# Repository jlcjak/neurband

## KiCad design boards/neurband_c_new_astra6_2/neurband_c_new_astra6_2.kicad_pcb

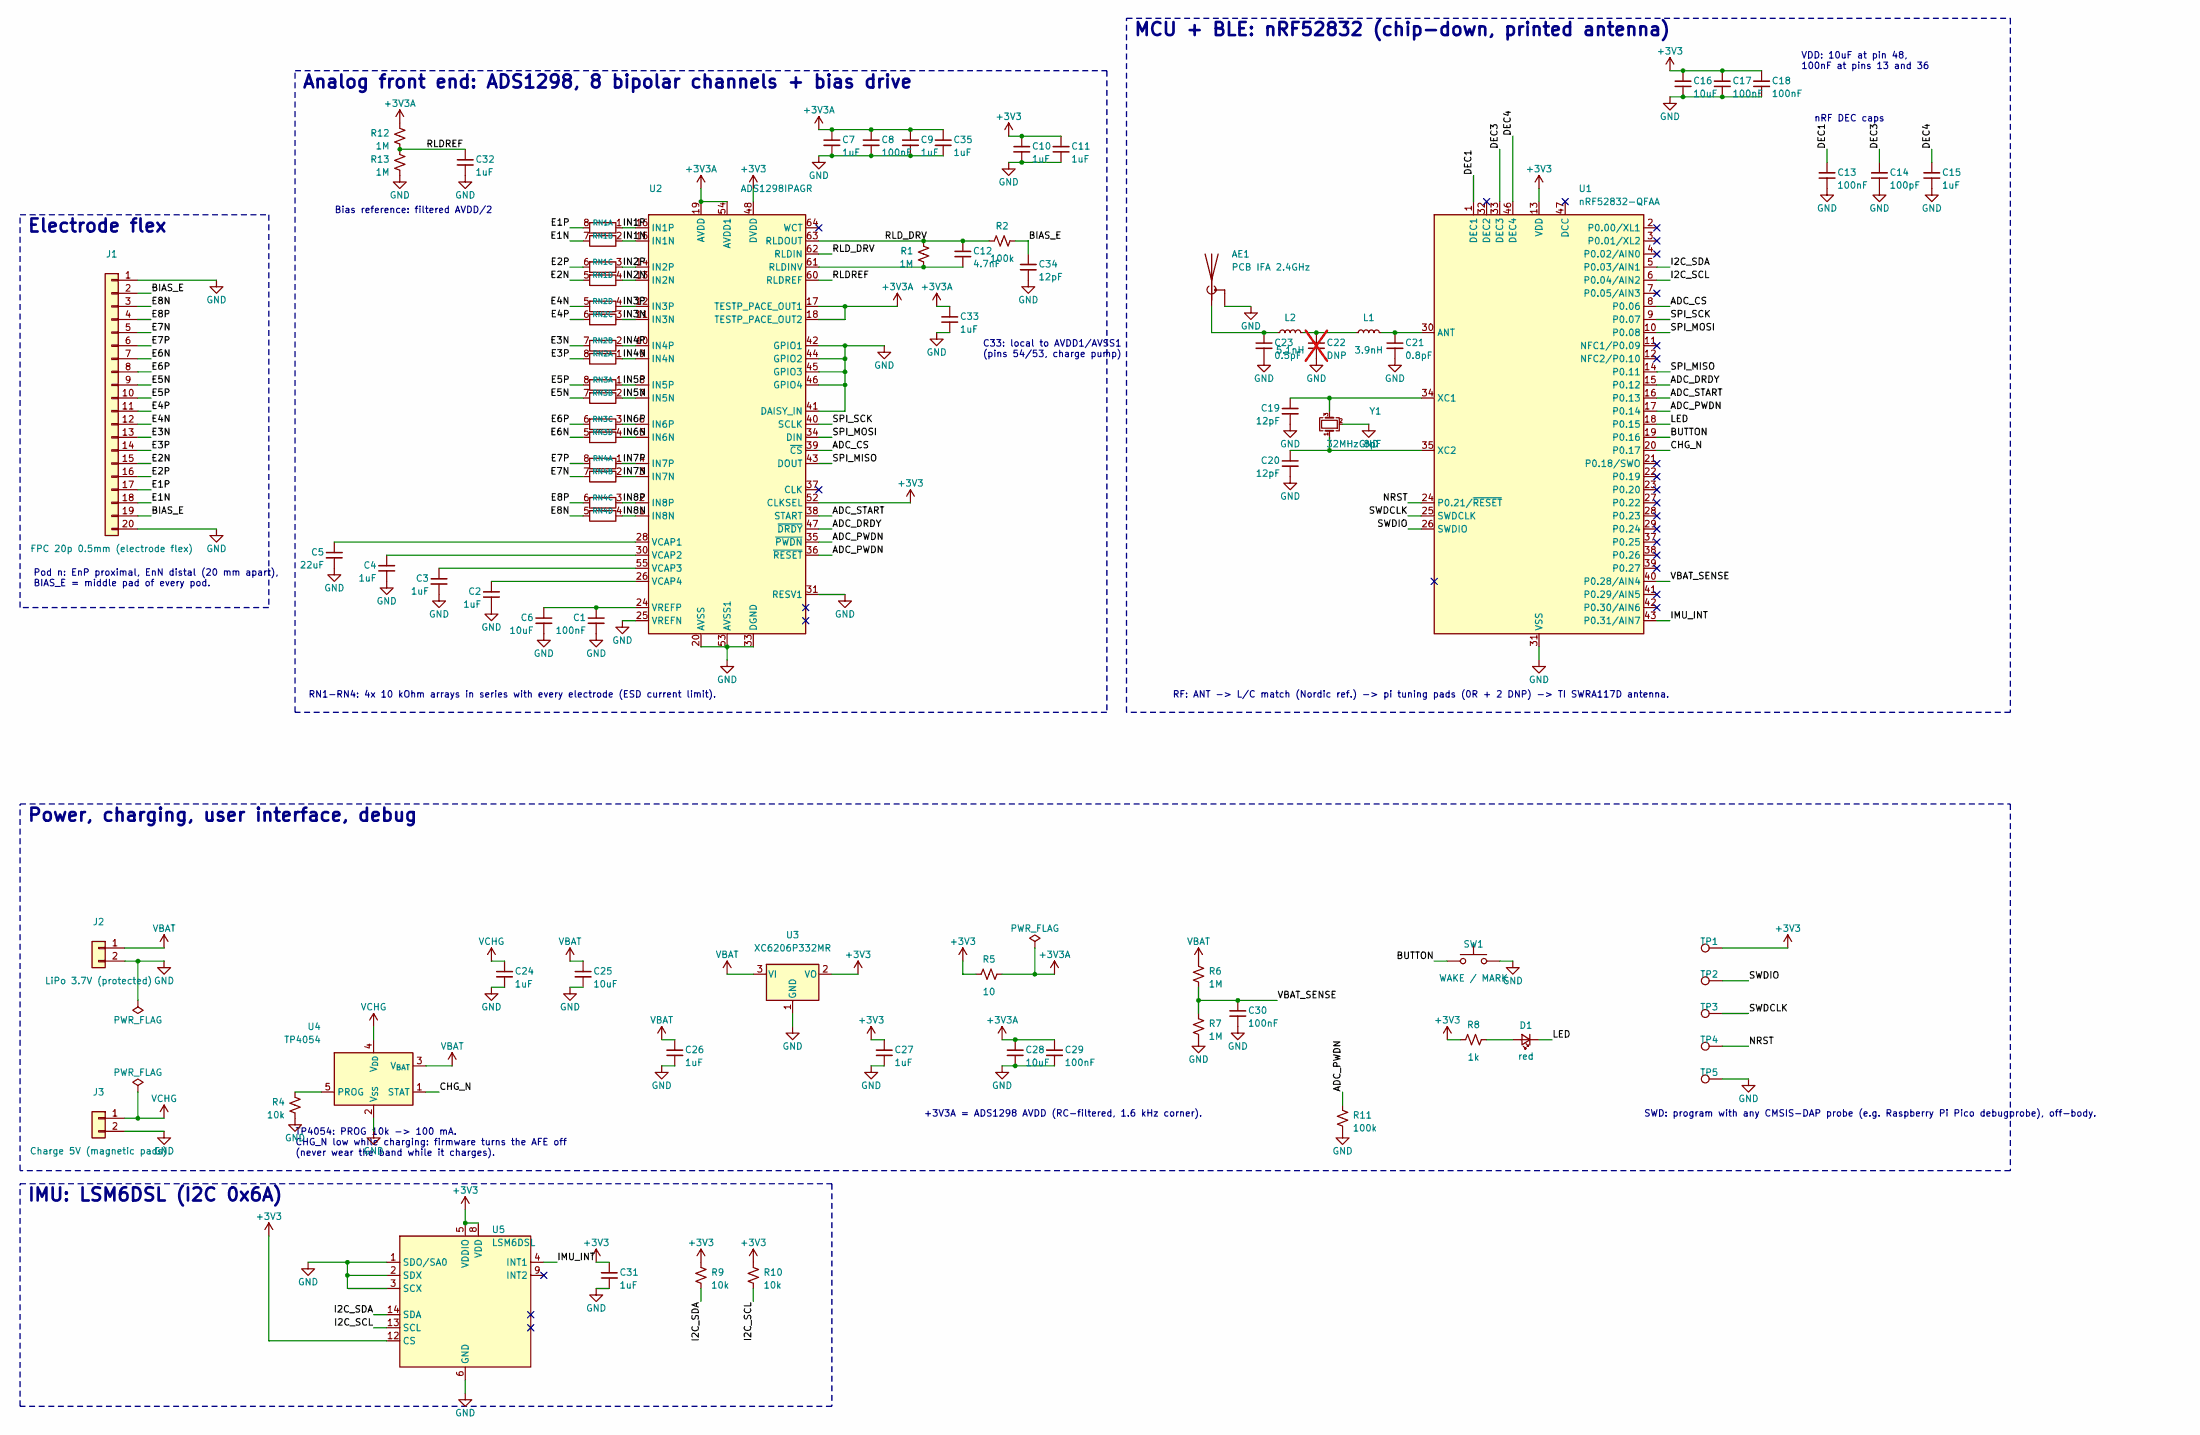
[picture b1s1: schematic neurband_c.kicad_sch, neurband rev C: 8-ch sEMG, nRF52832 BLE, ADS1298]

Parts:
AE1: PCB IFA 2.4GHz; Texas_SWRA117D_2.4GHz_Left
C1, C8, C13, C17, C18, C29, C30: 100nF; C_0402_Small; MPN CL05B104KO5NNNC; LCSC C1525
C2, C3, C4, C7, C9, C10, C11, C15, C24, C26, C27, C31, C32, C33, C35: 1uF; C_0402_Small; MPN CL05A105KA5NQNC; LCSC C52923
C5: 22uF; C_0603_Small; MPN CL10A226MQ8NRNC; LCSC C59461
C6, C16, C25, C28: 10uF; C_0603_Small; MPN CL10A106KP8NNNC; LCSC C19702
C12: 4.7nF; C_0402_Small; MPN 0402B472K500NT; LCSC C1538
C14: 100pF; C_0402_Small; MPN 0402CG101J500NT; LCSC C1546
C19, C20, C34: 12pF; C_0402_Small; MPN 0402CG120J500NT; LCSC C1547
C21: 0.8pF; C_0402_Small; MPN 0402CG0R8B500NT; LCSC C285068
C22: DNP; C_0402_Small; not fitted
C23: 0.5pF; C_0402_Small; MPN 0402CG0R5B500NT; LCSC C285052
D1: red; LED_0603_1608Metric; MPN KT-0603R; LCSC C2286
J1: FPC 20p 0.5mm (electrode flex); XUNPU_FPC-05F-20PH20_Centroid; MPN FPC-05F-20PH20; LCSC C2856803
J2: LiPo 3.7V (protected); WirePads_2x1.5x2mm_P3mm
J3: Charge 5V (magnetic pads); WirePads_2x1.5x2mm_P3mm
L1: 3.9nH; L_0402_Small; MPN SDCL1005C3N9STDF; LCSC C14033
L2: 5.1nH; L_0402_Small; MPN SDCL1005C5N1STDF; LCSC C33114
R1, R6, R7, R12, R13: 1M; R_0402_Small; MPN 0402WGF1004TCE; LCSC C26083
R2, R11: 100k; R_0402_Small; MPN 0402WGF1003TCE; LCSC C25741
R4, R9, R10: 10k; R_0402_Small; MPN 0402WGF1002TCE; LCSC C25744
R5: 10; R_0402_Small; MPN 0402WGF100JTCE; LCSC C25077
R8: 1k; R_0402_Small; MPN 0402WGF1001TCE; LCSC C11702
RN1, RN2, RN3, RN4: 10k; R_Array_Convex_4x0603_FabZero; MPN 4D03WGJ0103T5E; LCSC C29718
SW1: WAKE / MARK; SW_SPST_TS-1088-xR020; MPN TS-1088-AR02016; LCSC C720477
TP1, TP2, TP3, TP4, TP5: pad; SWD_Pad_1x1_P1.27
U1: nRF52832-QFAA; QFN-48-1EP_6x6mm_P0.4mm_EP4.6x4.6mm_FabZero; MPN NRF52832-QFAA-R; LCSC C77540
U2: ADS1298IPAGR; TQFP-64_10x10mm_P0.5mm_FabZero; MPN ADS1298IPAGR; LCSC C527440
U3: XC6206P332MR; SOT-23-3_FabZero; MPN XC6206P332MR-G; LCSC C5446
U4: TP4054; SOT-23-5_FabZero; MPN TP4054-42-SOT25R; LCSC C32574
U5: LSM6DSL; LGA-14_3x2.5mm_P0.5mm_LayoutBorder3x4y; MPN LSM6DSLTR; LCSC C126672
Y1: 32MHz 8pF; Crystal_SMD_2016-4Pin_2.0x1.6mm; MPN X201632MKB4SI; LCSC C718072

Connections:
+3V3: C10.1, C11.1, C16.1, C17.1, C18.1, C27.1, C31.1, R5.1, R8.1, R9.1, R10.1, TP1.1 (1_1), U1.13 (VDD), U1.36 (VDD), U1.48 (VDD), U2.48 (DVDD), U2.50 (DVDD), U2.52 (CLKSEL), U3.2 (VO), U5.5 (VDDIO), U5.8 (VDD), U5.12 (CS)
+3V3A: C7.1, C8.1, C9.1, C28.1, C29.1, C33.1, C35.1, R5.2, R12.1, U2.17 (TESTP_PACE_OUT1), U2.18 (TESTP_PACE_OUT2), U2.19 (AVDD), U2.21 (AVDD), U2.22 (AVDD), U2.54 (AVDD1), U2.56 (AVDD), U2.59 (AVDD)
/ADC_CS: U1.8 (P0.06), U2.39 (~CS)
/ADC_DRDY: U1.15 (P0.12), U2.47 (~DRDY)
/ADC_PWDN: R11.1, U1.17 (P0.14), U2.35 (~PWDN), U2.36 (~RESET)
/ADC_START: U1.16 (P0.13), U2.38 (START)
/BIAS_E: C34.1, J1.2, J1.19, R2.2
/BUTTON: SW1.1, U1.19 (P0.16)
/CHG_N: U1.20 (P0.17), U4.1 (STAT)
/DEC1: C13.1, U1.1 (DEC1)
/DEC3: C14.1, U1.33 (DEC3)
/DEC4: C15.1, U1.46 (DEC4)
/E1N: J1.18, RN1.7 (R2.2)
/E1P: J1.17, RN1.8 (R1.2)
/E2N: J1.15, RN1.5 (R4.2)
/E2P: J1.16, RN1.6 (R3.2)
/E3N: J1.13, RN2.7 (R2.2)
/E3P: J1.14, RN2.8 (R1.2)
/E4N: J1.12, RN2.5 (R4.2)
/E4P: J1.11, RN2.6 (R3.2)
/E5N: J1.9, RN3.7 (R2.2)
/E5P: J1.10, RN3.8 (R1.2)
/E6N: J1.7, RN3.5 (R4.2)
/E6P: J1.8, RN3.6 (R3.2)
/E7N: J1.5, RN4.7 (R2.2)
/E7P: J1.6, RN4.8 (R1.2)
/E8N: J1.3, RN4.5 (R4.2)
/E8P: J1.4, RN4.6 (R3.2)
/I2C_SCL: R10.2, U1.6 (P0.04/AIN2), U5.13 (SCL)
/I2C_SDA: R9.2, U1.5 (P0.03/AIN1), U5.14 (SDA)
/IMU_INT: U1.43 (P0.31/AIN7), U5.4 (INT1)
/IN1N: RN1.2 (R2.1), U2.15 (IN1N)
/IN1P: RN1.1 (R1.1), U2.16 (IN1P)
/IN2N: RN1.4 (R4.1), U2.13 (IN2N)
/IN2P: RN1.3 (R3.1), U2.14 (IN2P)
/IN3N: RN2.3 (R3.1), U2.11 (IN3N)
/IN3P: RN2.4 (R4.1), U2.12 (IN3P)
/IN4N: RN2.1 (R1.1), U2.9 (IN4N)
/IN4P: RN2.2 (R2.1), U2.10 (IN4P)
/IN5N: RN3.2 (R2.1), U2.7 (IN5N)
/IN5P: RN3.1 (R1.1), U2.8 (IN5P)
/IN6N: RN3.4 (R4.1), U2.5 (IN6N)
/IN6P: RN3.3 (R3.1), U2.6 (IN6P)
/IN7N: RN4.2 (R2.1), U2.3 (IN7N)
/IN7P: RN4.1 (R1.1), U2.4 (IN7P)
/IN8N: RN4.4 (R4.1), U2.1 (IN8N)
/IN8P: RN4.3 (R3.1), U2.2 (IN8P)
/LED: D1.1 (K), U1.18 (P0.15)
/NRST: TP4.1 (1_1), U1.24 (P0.21/~RESET)
/RLDREF: C32.1, R12.2, R13.1, U2.60 (RLDREF)
/RLD_DRV: C12.1, R1.1, R2.1, U2.62 (RLDIN), U2.63 (RLDOUT)
/SPI_MISO: U1.14 (P0.11), U2.43 (DOUT)
/SPI_MOSI: U1.10 (P0.08), U2.34 (DIN)
/SPI_SCK: U1.9 (P0.07), U2.40 (SCLK)
/SWDCLK: TP3.1 (1_1), U1.25 (SWDCLK)
/SWDIO: TP2.1 (1_1), U1.26 (SWDIO)
/VBAT_SENSE: C30.1, R6.2, R7.1, U1.40 (P0.28/AIN4)
GND: AE1.2 (Shield), C1.2, C2.2, C3.2, C4.2, C5.2, C6.2, C7.2, C8.2, C9.2, C10.2, C11.2, C13.2, C14.2, C15.2, C16.2, C17.2, C18.2, C19.2, C20.2, C21.2, C22.2, C23.2, C24.2, C25.2, C26.2, C27.2, C28.2, C29.2, C30.2, C31.2, C32.2, C33.2, C34.2, C35.2, J1.1, J1.20, J2.2, J3.2, R4.2, R7.2, R11.2, R13.2, SW1.2, TP5.1 (1_1), U1.31 (VSS), U1.45 (VSS), U1.49 (VSS), U2.20 (AVSS), U2.23 (AVSS), U2.25 (VREFN), U2.31 (RESV1), U2.32 (AVSS), U2.33 (DGND), U2.41 (DAISY_IN), U2.42 (GPIO1), U2.44 (GPIO2), U2.45 (GPIO3), U2.46 (GPIO4), U2.49 (DGND), U2.51 (DGND), U2.53 (AVSS1), U2.57 (AVSS), U2.58 (AVSS), U3.1 (GND), U4.2 (V_{SS}), U5.1 (SDO/SA0), U5.2 (SDX), U5.3 (SCX), U5.6 (GND), U5.7 (GND), Y1.2 (G), Y1.4 (G)
unnamed: AE1.1 (A), C23.1, L2.1
unnamed: C22.1, L1.1, L2.2
unnamed: D1.2 (A), R8.2
unnamed: C21.1, L1.2, U1.30 (ANT)
unnamed: C19.1, U1.34 (XC1), Y1.3
unnamed: C20.1, U1.35 (XC2), Y1.1
unnamed: C12.2, R1.2, U2.61 (RLDINV)
unnamed: C5.1, U2.28 (VCAP1)
unnamed: C4.1, U2.30 (VCAP2)
unnamed: C3.1, U2.55 (VCAP3)
unnamed: C2.1, U2.26 (VCAP4)
unnamed: C1.1, C6.1, U2.24 (VREFP)
unnamed: R4.1, U4.5 (PROG)
VBAT: C25.1, C26.1, J2.1, R6.1, U3.3 (VI), U4.3 (V_{BAT})
VCHG: C24.1, J3.1, U4.4 (V_{DD})

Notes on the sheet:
Analog front end: ADS1298, 8 bipolar channels + bias drive
C33: local to AVDD1/AVSS1 (pins 54/53, charge pump)
VDD: 10uF at pin 48, 100nF at pins 13 and 36
nRF DEC caps
MCU + BLE: nRF52832 (chip-down, printed antenna)
TP4054: PROG 10k -> 100 mA. CHG_N low while charging: firmware turns the AFE off (never wear the band while it charges).
IMU: LSM6DSL (I2C 0x6A)
Pod n: EnP proximal, EnN distal (20 mm apart), BIAS_E = middle pad of every pod.
Bias reference: filtered AVDD/2
RN1-RN4: 4x 10 kOhm arrays in series with every electrode (ESD current limit).
Electrode flex
Power, charging, user interface, debug
+3V3A = ADS1298 AVDD (RC-filtered, 1.6 kHz corner).
SWD: program with any CMSIS-DAP probe (e.g. Raspberry Pi Pico debugprobe), off-body.
RF: ANT -> L/C match (Nordic ref.) -> pi tuning pads (0R + 2 DNP) -> TI SWRA117D antenna.

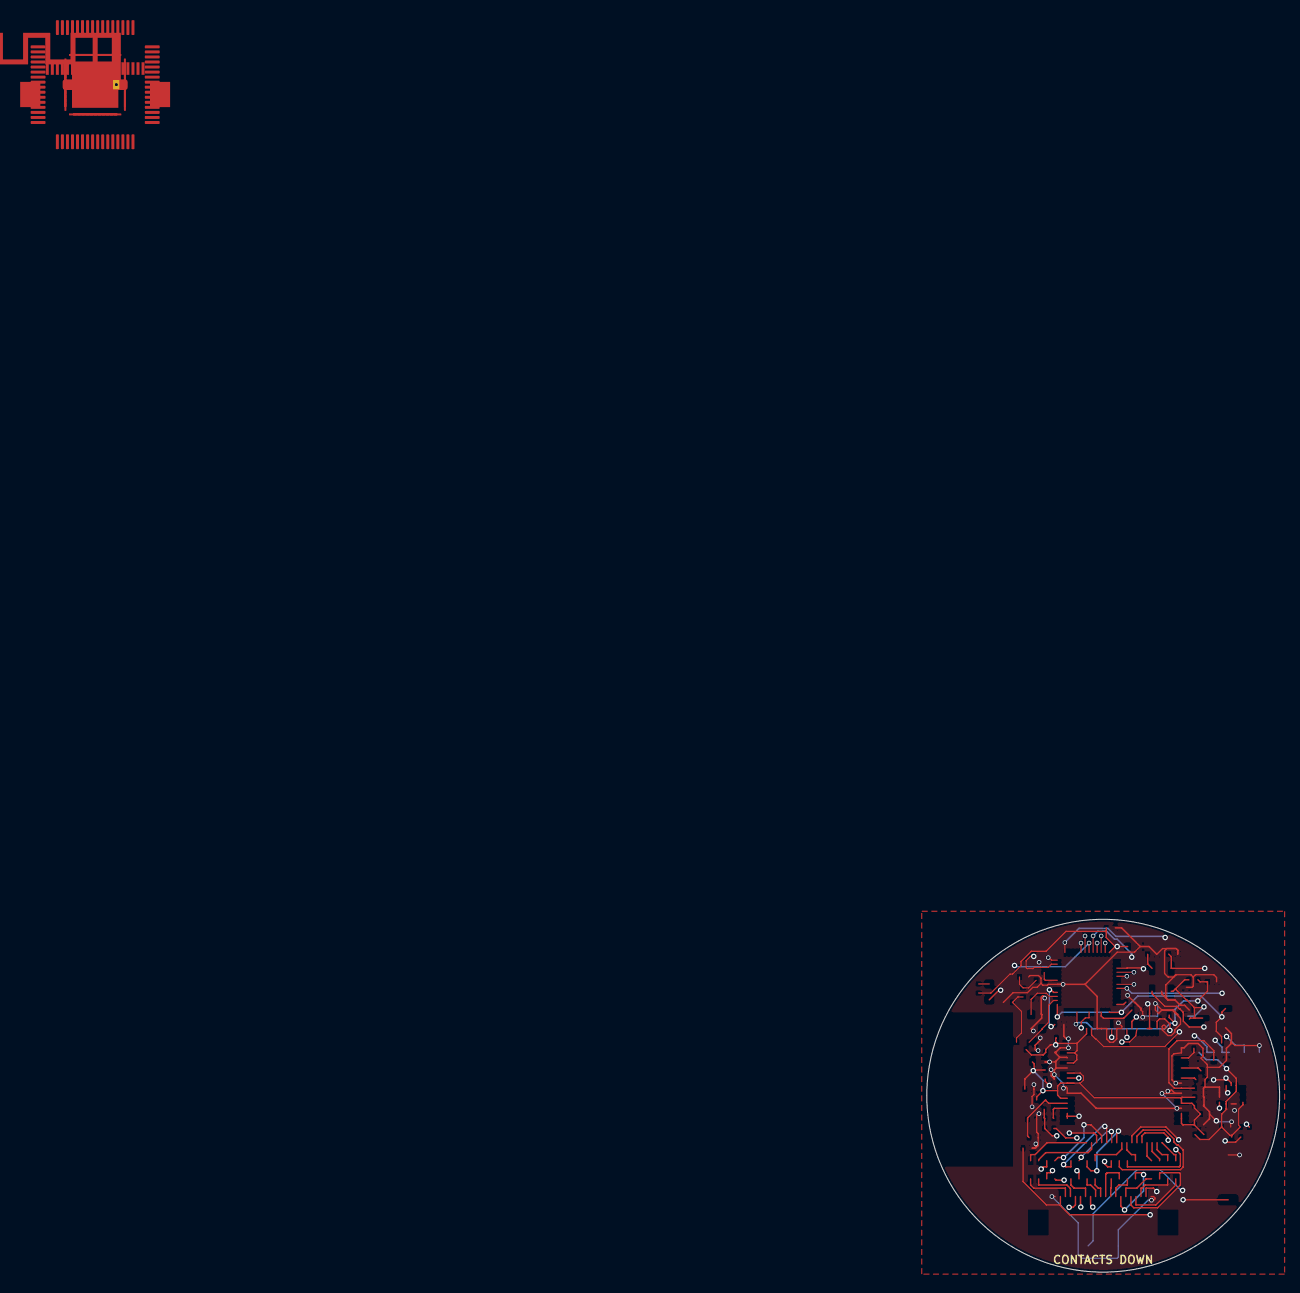
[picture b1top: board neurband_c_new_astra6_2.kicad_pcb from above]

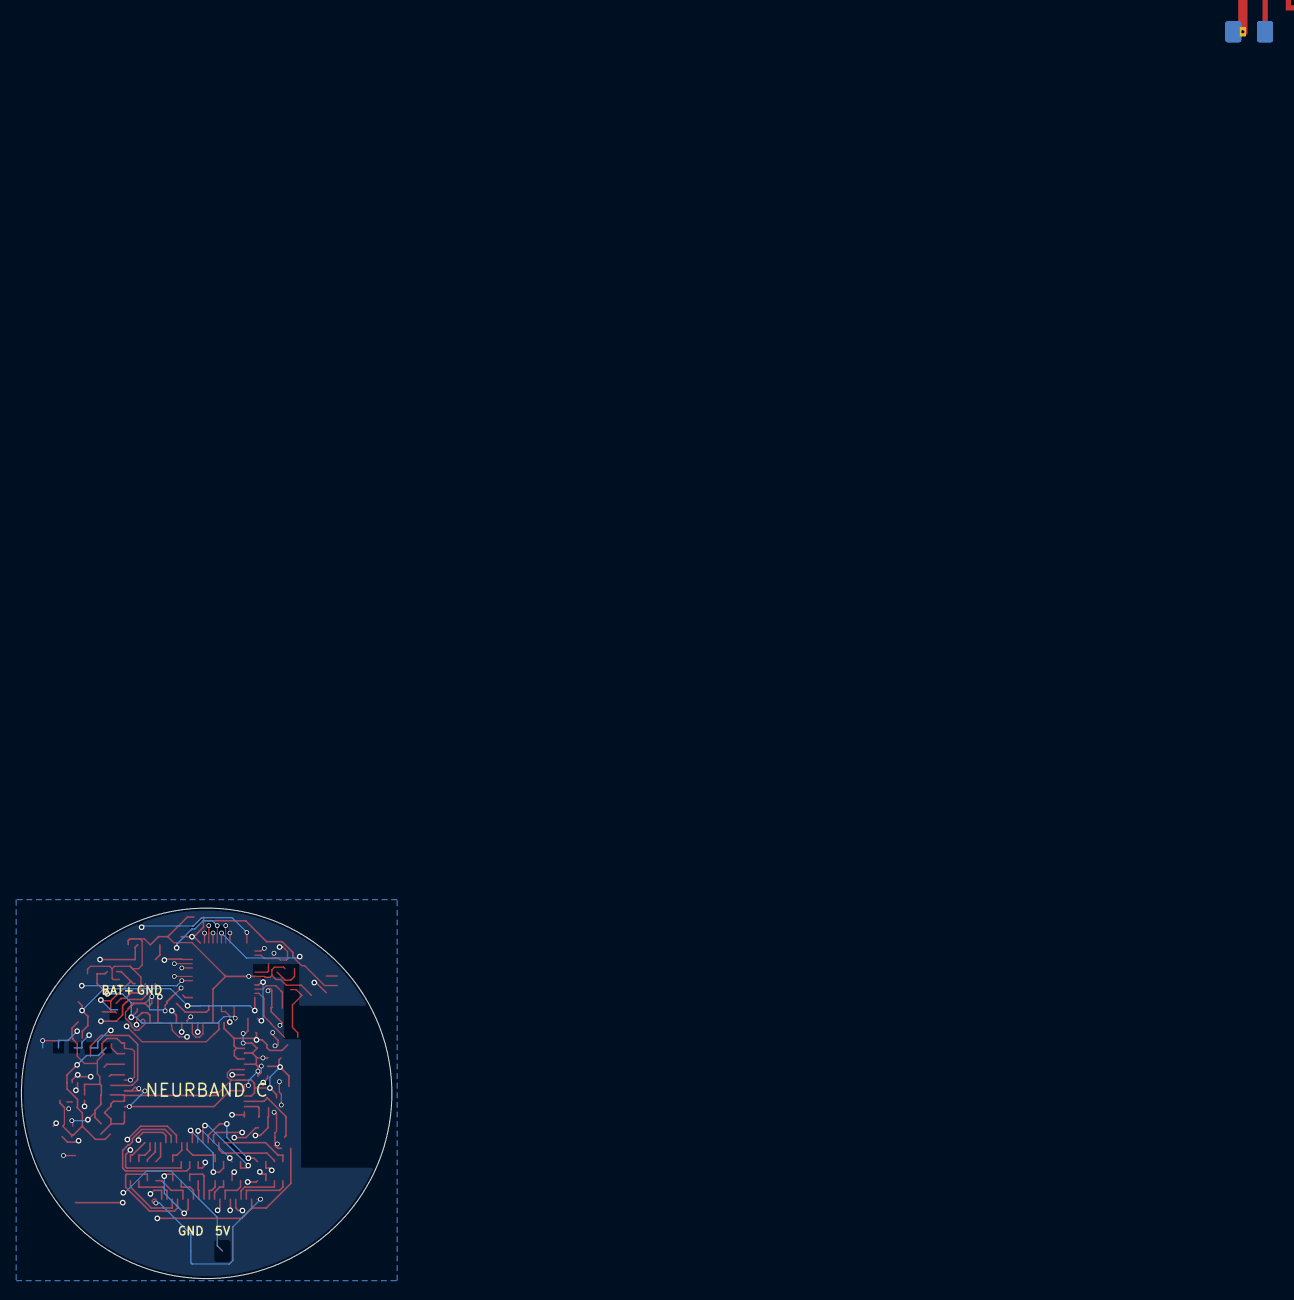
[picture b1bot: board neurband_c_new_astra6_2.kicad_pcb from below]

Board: 4 copper layers, 35.0 x 35.0 mm, 70 parts (7 on the bottom side), 73 nets.

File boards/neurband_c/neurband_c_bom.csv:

"Reference","Value","Footprint","MPN","LCSC","QUANTITY"
"C1,C8,C13,C17,C18,C29,C30","100nF","neurband:C_0402_Small","CL05B104KO5NNNC","C1525","7"
"C2-C4,C7,C9-C11,C15,C24,C26,C27,C31-C33,C35","1uF","neurband:C_0402_Small","CL05A105KA5NQNC","C52923","15"
"C5","22uF","neurband:C_0603_Small","CL10A226MQ8NRNC","C59461","1"
"C6,C16,C25,C28","10uF","neurband:C_0603_Small","CL10A106KP8NNNC","C19702","4"
"C12","4.7nF","neurband:C_0402_Small","0402B472K500NT","C1538","1"
"C14","100pF","neurband:C_0402_Small","0402CG101J500NT","C1546","1"
"C19,C20,C34","12pF","neurband:C_0402_Small","0402CG120J500NT","C1547","3"
"C21","0.8pF","neurband:C_0402_Small","0402CG0R8B500NT","C285068","1"
"C23","0.5pF","neurband:C_0402_Small","0402CG0R5B500NT","C285052","1"
"D1","red","LED_SMD:LED_0603_1608Metric","KT-0603R","C2286","1"
"J1","FPC 20p 0.5mm (electrode flex)","neurband:XUNPU_FPC-05F-20PH20_Centroid","FPC-05F-20PH20","C2856803","1"
"L1","3.9nH","neurband:L_0402_Small","SDCL1005C3N9STDF","C14033","1"
"L2","5.1nH","neurband:L_0402_Small","SDCL1005C5N1STDF","C33114","1"
"R1,R6,R7,R12,R13","1M","neurband:R_0402_Small","0402WGF1004TCE","C26083","5"
"R2,R11","100k","neurband:R_0402_Small","0402WGF1003TCE","C25741","2"
"R4,R9,R10","10k","neurband:R_0402_Small","0402WGF1002TCE","C25744","3"
"R5","10","neurband:R_0402_Small","0402WGF100JTCE","C25077","1"
"R8","1k","neurband:R_0402_Small","0402WGF1001TCE","C11702","1"
"RN1-RN4","10k","neurband:R_Array_Convex_4x0603_FabZero","4D03WGJ0103T5E","C29718","4"
"SW1","WAKE / MARK","Button_Switch_SMD:SW_SPST_TS-1088-xR020","TS-1088-AR02016","C720477","1"
"U1","nRF52832-QFAA","neurband:QFN-48-1EP_6x6mm_P0.4mm_EP4.6x4.6mm_FabZero","NRF52832-QFAA-R","C77540","1"
"U2","ADS1298IPAGR","neurband:TQFP-64_10x10mm_P0.5mm_FabZero","ADS1298IPAGR","C527440","1"
"U3","XC6206P332MR","neurband:SOT-23-3_FabZero","XC6206P332MR-G","C5446","1"
"U4","TP4054","neurband:SOT-23-5_FabZero","TP4054-42-SOT25R","C32574","1"
"U5","LSM6DSL","Package_LGA:LGA-14_3x2.5mm_P0.5mm_LayoutBorder3x4y","LSM6DSLTR","C126672","1"
"Y1","32MHz 8pF","Crystal:Crystal_SMD_2016-4Pin_2.0x1.6mm","X201632MKB4SI","C718072","1"
